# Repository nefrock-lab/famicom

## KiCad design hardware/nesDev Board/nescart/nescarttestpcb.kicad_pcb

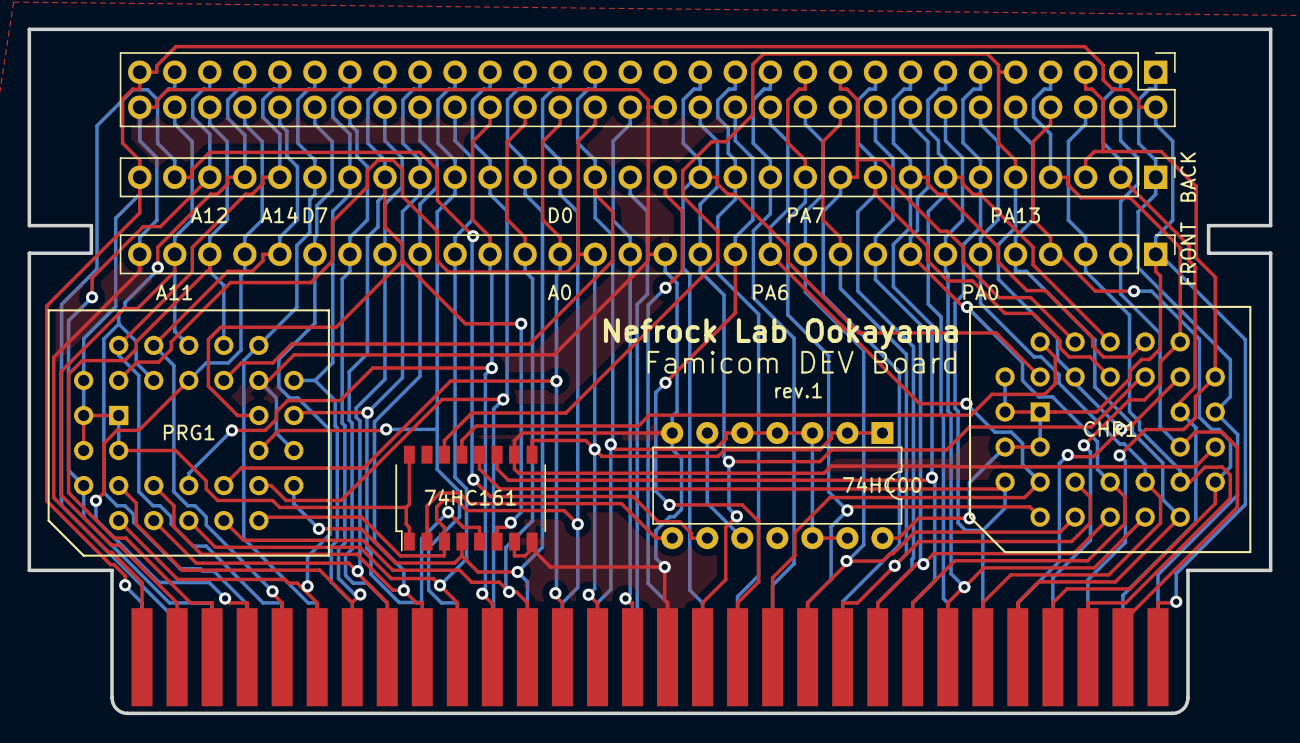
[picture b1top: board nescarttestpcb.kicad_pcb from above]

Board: 2 copper layers, 90.0 x 49.6 mm, 8 parts (0 on the bottom side), 61 nets.

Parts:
74HC00: 74LS00; DIP-14_W7.62mm
74HC161: 74LS161; SOP-16_4.4x10.4mm_Pitch1.27mm
BACK: CONN_01X30; Pin_Header_Straight_1x30_Pitch2.54mm
CHR1: EN29F002T; PLCC32
CONN1: famicom_card_test; FAMICOMcommnotext
FRONT: CONN_01X30; Pin_Header_Straight_1x30_Pitch2.54mm
PIN: CONN_02X30; Pin_Header_Straight_2x30_Pitch2.54mm
PRG1: EN29F002T; PLCC32

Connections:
/IRQ: CONN1.46, FRONT.16, PIN.32
/PA13: BACK.12, CONN1.12, PIN.23
/RD: CHR1.24, CONN1.44, FRONT.14, PIN.28
/ROMSEL: 74HC00.3, 74HC00.4, 74HC00.5, 74HC00.12, 74HC00.13, BACK.17, CONN1.17, PIN.33, PRG1.24
/VRAM_CS: BACK.13, CONN1.13, PIN.25
/WE: BACK.14, CHR1.31, CONN1.14, PIN.27
A0: CONN1.48, FRONT.18, PIN.36, PRG1.12
A1: CONN1.49, FRONT.19, PIN.38, PRG1.11
A2: CONN1.50, FRONT.20, PIN.40, PRG1.10
A3: CONN1.51, FRONT.21, PIN.42, PRG1.9
A4: CONN1.52, FRONT.22, PIN.44, PRG1.8
A5: CONN1.53, FRONT.23, PIN.46, PRG1.7
A6: CONN1.54, FRONT.24, PIN.48, PRG1.6
A7: CONN1.55, FRONT.25, PIN.50, PRG1.5
A8: CONN1.56, FRONT.26, PIN.52, PRG1.27
A9: CONN1.57, FRONT.27, PIN.54, PRG1.26
A10: CONN1.58, FRONT.28, PIN.56, PRG1.23
A11: CONN1.59, FRONT.29, PIN.58, PRG1.25
A12: BACK.28, CONN1.28, PIN.55, PRG1.4
A13: BACK.27, CONN1.27, PIN.53, PRG1.28
A14: BACK.26, CONN1.26, PIN.51, PRG1.29
CK: 74HC00.8, 74HC161.2
D0: 74HC161.3, BACK.18, CONN1.18, PIN.35, PRG1.13
D1: 74HC161.4, BACK.19, CONN1.19, PIN.37, PRG1.14
D2: BACK.20, CONN1.20, PIN.39, PRG1.15
D3: BACK.21, CONN1.21, PIN.41, PRG1.17
D4: 74HC161.5, BACK.22, CONN1.22, PIN.43, PRG1.18
D5: 74HC161.6, BACK.23, CONN1.23, PIN.45, PRG1.19
D6: BACK.24, CONN1.24, PIN.47, PRG1.20
D7: BACK.25, CONN1.25, PIN.49, PRG1.21
F2: 74HC00.9, BACK.29, CONN1.29, PIN.57
GND: 74HC00.7, 74HC161.7, 74HC161.8, 74HC161.10, CHR1.16, CONN1.45, CONN1.60, FRONT.15, FRONT.30, PIN.30, PIN.60, PRG1.16, PRG1.22
unnamed: 74HC00.6, 74HC00.10
PA0: CHR1.12, CONN1.36, FRONT.6, PIN.12
PA1: CHR1.11, CONN1.37, FRONT.7, PIN.14
PA2: CHR1.10, CONN1.38, FRONT.8, PIN.16
PA3: CHR1.9, CONN1.39, FRONT.9, PIN.18
PA4: CHR1.8, CONN1.40, FRONT.10, PIN.20
PA5: CHR1.7, CONN1.41, FRONT.11, PIN.22
PA6: CHR1.6, CONN1.42, FRONT.12, PIN.24
PA7: BACK.11, CHR1.5, CONN1.11, PIN.21
PA8: BACK.10, CHR1.27, CONN1.10, PIN.19
PA9: BACK.9, CHR1.26, CONN1.9, PIN.17
PA10: 74HC161.11, BACK.8, CHR1.23, CONN1.8, PIN.15
PA11: BACK.7, CHR1.25, CONN1.7, PIN.13
PA12: 74HC161.12, BACK.6, CHR1.4, CONN1.6, PIN.11
PA13: 74HC161.14, BACK.5, CHR1.22, CHR1.28, CONN1.5, PIN.9
PA14: 74HC161.13, CHR1.29
PD0: CHR1.13, CONN1.35, FRONT.5, PIN.10
PD1: CHR1.14, CONN1.34, FRONT.4, PIN.8
PD2: CHR1.15, CONN1.33, FRONT.3, PIN.6
PD3: CHR1.17, CONN1.32, FRONT.2, PIN.4
PD4: BACK.1, CHR1.18, CONN1.1, PIN.1
PD5: BACK.2, CHR1.19, CONN1.2, PIN.3
PD6: BACK.3, CHR1.20, CONN1.3, PIN.5
PD7: BACK.4, CHR1.21, CONN1.4, PIN.7
R/W: 74HC00.1, 74HC00.2, 74HC161.9, CONN1.47, FRONT.17, PIN.34, PRG1.31
SOUND_I: BACK.16, CONN1.16
SOUND_O: BACK.15, CONN1.15
VCC: 74HC00.14, 74HC161.1, 74HC161.16, BACK.30, CHR1.1, CHR1.2, CHR1.3, CHR1.30, CHR1.32, CONN1.30, CONN1.31, FRONT.1, PIN.2, PIN.59, PRG1.1, PRG1.2, PRG1.3, PRG1.30, PRG1.32
VRAM_A10: CONN1.43, FRONT.13, PIN.26

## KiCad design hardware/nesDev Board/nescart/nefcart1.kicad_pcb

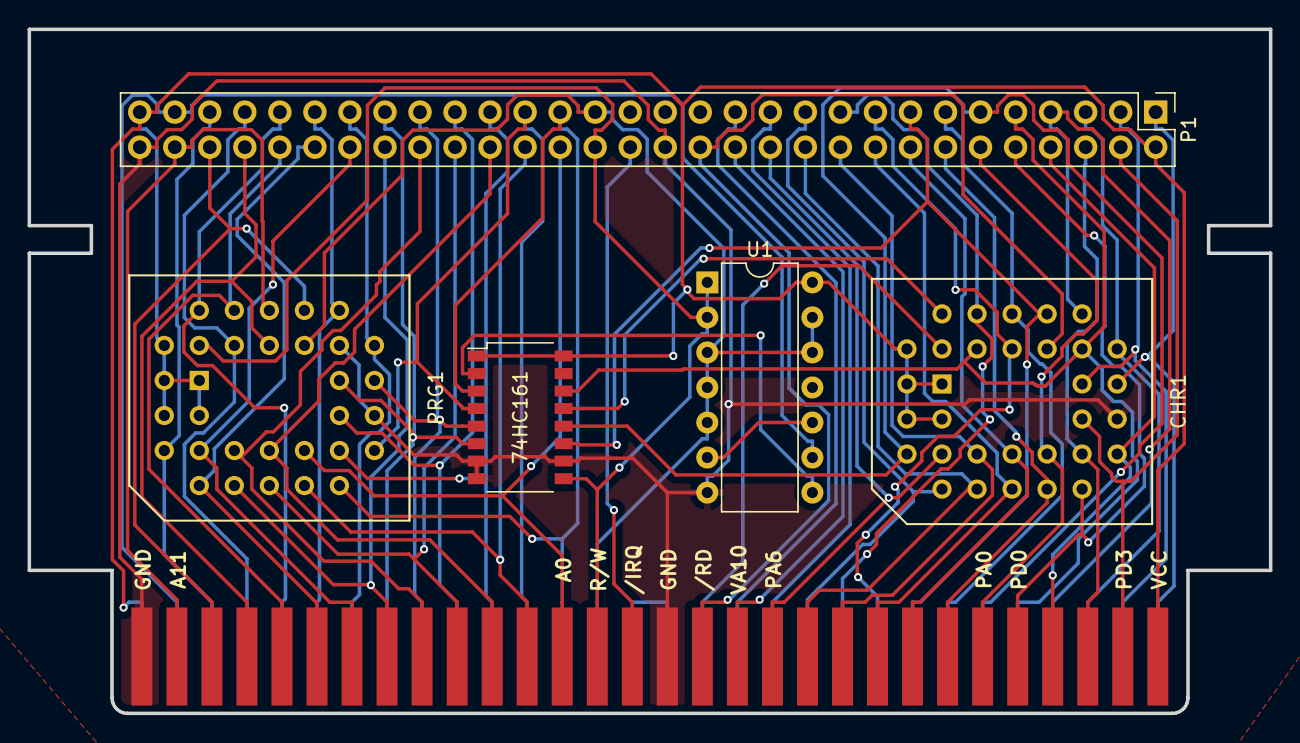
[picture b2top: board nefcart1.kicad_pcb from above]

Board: 2 copper layers, 90.0 x 49.6 mm, 5 parts (0 on the bottom side), 54 nets.

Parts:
74HC161: 74LS161; SOP-16_4.4x10.4mm_Pitch1.27mm
CHR1: EN29F002T; PLCC32
P1: CONN_02X30; Pin_Header_Straight_2x30_Pitch2.54mm
PRG1: EN29F002T; PLCC32
U1: 74LS00; DIP-14_W7.62mm

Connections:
/RD: CHR1.24, P1.28
/ROMSEL: P1.33, PRG1.24, U1.3, U1.4, U1.5, U1.12, U1.13
A0: P1.36, PRG1.12
A1: P1.38, PRG1.11
A2: P1.40, PRG1.10
A3: P1.42, PRG1.9
A4: P1.44, PRG1.8
A5: P1.46, PRG1.7
A6: P1.48, PRG1.6
A7: P1.50, PRG1.5
A8: P1.52, PRG1.27
A9: P1.54, PRG1.26
A10: P1.56, PRG1.23
A11: P1.58, PRG1.25
A12: P1.55, PRG1.4
A13: P1.53, PRG1.28
A14: P1.51, PRG1.29
CK: 74HC161.2, U1.8
D0: 74HC161.3, P1.35, PRG1.13
D1: 74HC161.4, P1.37, PRG1.14
D2: P1.39, PRG1.15
D3: P1.41, PRG1.17
D4: 74HC161.5, P1.43, PRG1.18
D5: 74HC161.6, P1.45, PRG1.19
D6: P1.47, PRG1.20
D7: P1.49, PRG1.21
F2: P1.57, U1.9
GND: 74HC161.7, 74HC161.8, 74HC161.10, CHR1.16, P1.30, P1.60, PRG1.16, PRG1.22, U1.7
unnamed: U1.6, U1.10
PA0: CHR1.12, P1.12
PA1: CHR1.11, P1.14
PA2: CHR1.10, P1.16
PA3: CHR1.9, P1.18
PA4: CHR1.8, P1.20
PA5: CHR1.7, P1.22
PA6: CHR1.6, P1.24
PA7: CHR1.5, P1.21
PA8: CHR1.27, P1.19
PA9: CHR1.26, P1.17
PA10: 74HC161.11, CHR1.23, P1.15
PA11: CHR1.25, P1.13
PA12: 74HC161.12, CHR1.4, P1.11
PA13: 74HC161.14, CHR1.22, CHR1.28, P1.9
PA14: 74HC161.13, CHR1.29
PD0: CHR1.13, P1.10
PD1: CHR1.14, P1.8
PD2: CHR1.15, P1.6
PD3: CHR1.17, P1.4
PD4: CHR1.18, P1.1
PD5: CHR1.19, P1.3
PD6: CHR1.20, P1.5
PD7: CHR1.21, P1.7
R/W: 74HC161.9, P1.34, PRG1.31, U1.1, U1.2
VCC: 74HC161.1, 74HC161.16, CHR1.1, CHR1.2, CHR1.3, CHR1.30, CHR1.32, P1.2, P1.59, PRG1.1, PRG1.2, PRG1.3, PRG1.30, PRG1.32, U1.14

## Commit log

2017-03-06 CAD UPDATE
    add CAD
2017-03-06 Revert "CAD UPDATE"
    This reverts commit e8649841f3d1ea3aa0480a9010c7c33141bd5911.
2017-03-06 Create test
2017-03-17 cad
    add cad
